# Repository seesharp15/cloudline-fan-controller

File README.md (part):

# Cloudline AI-CLS6 fan controller

A stand-alone speed controller for the **AC Infinity Cloudline AI-CLS6**
(Cloudline S6) EC inline fan. It uses an **Arduino Nano** and an **AITRIP
1.3″ OLED module with a built-in EC11 rotary encoder**, plugs into the fan's
4-pin Molex control lead in place of the stock controller, and runs entirely
from the fan's own 10 V supply.

| Fan off | Fan running (calibrated) |
|---|---|
|  |  |

## What it does

- **Turn the knob** to set the speed from 0 to 100 %: 1 % per click, or 5 %
  per click when you spin it quickly.
- **Press the knob** to switch the fan on or off.
- **The fan is always off at power-up.** A resistor guarantees this in
  hardware before the Arduino even starts, and the firmware starts OFF.
- **The speed setting is kept while the controller has power.** Off and on
  again returns to the same speed. After a power cut it starts OFF at 50 %.
  Nothing is stored permanently.
- **The display shows:**
  - ON/OFF status in the title bar, which turns solid while the fan is on;
  - **SET**: the speed you asked for, as a bar and a percentage;
  - **ACT**: the measured speed from the fan's tachometer, as a bar and a
    percentage of the fan's calibrated top speed;
  - the measured **RPM**.
- **Power:** taken from the fan's +10 V through a resettable fuse,
  reverse-polarity diode, surge clamp and filtering. The controller draws
  about 35–60 mA.
- **Safety nets:** a watchdog stops the fan and restarts the controller if
  the program ever hangs; a "NO TACH / STALLED" warning appears if the fan is
  told to run but no speed pulses arrive.

> ⚠️ **Read before you build.** AC Infinity does not publish the electrical
> details of the control port. The pin functions and signal levels in this
> project come from other builders' reports, and **whether the 4-pin port
> carries a tachometer signal at all is unconfirmed**. The
> [pre-connection verification](#pre-connection-verification) below takes
> about 20 minutes with a multimeter and tells you whether your fan matches.
> Without a tach signal everything works except the ACT bar and RPM.
> [VERIFICATION.md](VERIFICATION.md) lists exactly what has and has not been
> verified.

## Contents

1. [Documents in this repository](#documents-in-this-repository)
2. [Bill of materials](#bill-of-materials)
3. [Tools](#tools)
4. [Software setup](#software-setup)
5. [Pre-connection verification](#pre-connection-verification)
6. [Step-by-step build](#step-by-step-build) (steps 1–6, then
   [7. first power-up](#step-7-first-power-up-on-the-fan-supply) and
   [8. enclosure](#step-8-fit-it-in-the-enclosure))
8. [Normal operation](#normal-operation)
9. [Troubleshooting](#troubleshooting)
10. [Development and tests](#development-and-tests)
11. [Sources](#sources)

---

## Documents in this repository

| Document | Contents |
|---|---|
| [PINOUT.md](PINOUT.md) | Every pin of every part, power rails, point-to-point wiring list |
| [hardware/schematic.svg](hardware/schematic.svg) ([PNG](hardware/schematic.png)) | Full schematic, every part labelled with reference and value |
| [hardware/wiring.svg](hardware/wiring.svg) ([PNG](hardware/wiring.png)) | Physical wiring view with suggested wire colours, for people who don't read schematics |
| [hardware/bom.csv](hardware/bom.csv) | Parts list with part numbers and prices |
| [hardware/pcb/](hardware/pcb/README.md) | **Single-sided PCB** (1 copper layer) as an alternative to perfboard: KiCad project, Gerbers + drill ready to order, assembly drawing, ordering options |
| [hardware/pcb/fusion/](hardware/pcb/fusion/README.md) | **Milling the PCB in Fusion 360** on a Stepcraft M.1000: STEP + DXF (isolation paths, drill layers), Fusion tool library, CAM setup for UCCNC |
| [hardware/pcb/eagle/](hardware/pcb/eagle/README.md) | **Editable design for Fusion Electronics**: schematic + board in EAGLE format |
| [FAQ.md](FAQ.md) | The questions builders ask: USB + fan power, PWM frequency, other fans, warranty, other boards… |
| [BENCH_TEST.md](BENCH_TEST.md) | Manual test of every requirement, first with a dummy load, then with the fan |
| [VERIFICATION.md](VERIFICATION.md) | Requirements traceability, electrical calculations, pin cross-check, what is verified versus assumed, known limitations, review findings |
| [CHANGELOG.md](CHANGELOG.md) | Changes |
| [firmware/](firmware/) | Arduino sketch. Every setting is in [`config.h`](firmware/cloudline_controller/config.h) |
| [test/](test/) | Host unit tests and simulations ([how to run](test/README.md)) |
| [sim/](sim/) | Wokwi simulator files ([what can and cannot be simulated](sim/README.md)) |

---

## Bill of materials

Prices are approximate (USD, 2026) for single quantities. The full list with
manufacturer part numbers is in [hardware/bom.csv](hardware/bom.csv). Any
part with the same value and rating works; the part numbers are examples.

| Ref | Qty | Part | Value / rating | Example part number | ≈ Cost |
|---|---|---|---|---|---|
| U1 | 1 | Arduino Nano | ATmega328P, 5 V, 16 MHz (CH340 clone is fine) | Arduino A000005, or ELEGOO Nano V3.0 | $8 (clone) |
| U3 | 1 | 1.3″ OLED + EC11 module | SH1106, 128×64, I²C 0x3C, 3.3 V | AITRIP 1.3″ OLED with EC11 (Amazon ASIN B0F87DZ51P) | $10 |
| U2 | 1 | 3.3 V LDO regulator | 250 mA, V<sub>in</sub> ≤ 6 V, TO-92 | Microchip MCP1700-3302E/TO | $0.45 |
| Q1 | 1 | N-channel MOSFET | 60 V, 200 mA, logic-level, TO-92 | onsemi 2N7000TA | $0.30 |
| D1 | 1 | Schottky diode | 1 A, 20 V | 1N5817 | $0.20 |
| D2 | 1 | TVS diode, unidirectional | V<sub>RWM</sub> 11.1 V, 600 W | Littelfuse P6KE13A (P6KE15A if your fan measures > 10.8 V) | $0.45 |
| D3, D4 | 2 | Small Schottky diode | 30 V, 200 mA | BAT85 | $0.30 |
| F1 | 1 | Resettable PTC fuse | 0.2 A hold, 0.4 A trip | Bourns MF-R020 | $0.35 |
| U4 | 1 | I²C level shifter module (BSS138) | 5 V ↔ 3.3 V, bidirectional, 2 channels used | SparkFun BOB-12009 | $4 |
| C1 | 1 | Electrolytic capacitor | 220 µF, 25 V | Panasonic EEU-FR1E221 | $0.40 |
| C2 | 1 | Ceramic capacitor | 100 nF, 50 V, 5 mm lead pitch | TDK FG28X7R1H104KNT06 | $0.25 |
| C3, C4 | 2 | Ceramic capacitor | 1 µF, 25 V, 5 mm lead pitch | TDK FG28X7R1E105KRT06 | $0.60 |
| C5 | 1 | Ceramic capacitor | 10 nF, 50 V, 5 mm lead pitch | TDK FG28X7R1H103KNT06 | $0.25 |
| R1, R2 | 2 | Resistor ¼ W 5 % | 2.2 kΩ | Yageo CFR-25JB-52-2K2 | $0.20 |
| R3 | 1 | Resistor ¼ W 5 % | 220 Ω | Yageo CFR-25JB-52-220R | $0.10 |
| R4, R6 | 2 | Resistor ¼ W 5 % | 10 kΩ | Yageo CFR-25JB-52-10K | $0.20 |
| R5 | (1) | Resistor ¼ W 5 %, **only if check M3 says so** | 4.7 kΩ | Yageo CFR-25JB-52-4K7 | $0.10 |
| R7 | 1 | Resistor ¼ W 5 % | 1 kΩ | Yageo CFR-25JB-52-1K0 | $0.10 |
| J1 | 1 | 4-pin PC "Molex" extension cable | male-to-female, 18–20 AWG | StarTech.com LP4POWEXT12 | $4 |
| — | 1 | Perfboard | 5 × 7 cm, 2.54 mm pitch | any | $1 |
| — | 2 | Female header strip (Nano socket) | 1 × 15, 2.54 mm | Sullins PPTC151LFBN-RC | $2 |
| — | 10 | Female-female jumper wires | 20 cm Dupont, for the OLED module | any | $3 |
| — | — | Hook-up wire | 22 AWG stranded (power), 24–26 AWG stranded (signals), several colours | any silicone wire kit | $8 |
| — | — | Heat-shrink tubing | 2–6 mm assortment, 2:1 | any | $6 |
| — | 1 | Enclosure | ABS box, **inside** at least 75 × 60 × 35 mm (perfboard) or 115 × 90 × 35 mm (PCB, so its corners clear the box's screw posts) | a Hammond 1591-series size chosen from its drawing, or 3D-printed | $8 |
| — | 1 | Cable gland | PG7 | any | $0.50 |
| — | 4 | Nylon standoffs and screws | M2.5 or M3 | any | $1 |
| | | | | **Total** | **≈ $60** |

## Tools

| Tool | Notes |
|---|---|
| Temperature-controlled soldering iron | 330–360 °C, small chisel tip |
| Solder | 0.6–0.8 mm rosin-core |
| **Digital multimeter** | Must measure DC volts, resistance, continuity and **diode test**. A frequency (Hz) range is useful for the tach check but not essential. |
| Wire strippers, flush cutters, tweezers | |
| Heat gun or lighter | For heat-shrink |
| **USB cable for the Nano** | Usually **Mini-USB** (some clones use Micro-USB or USB-C). It must be a **data** cable, not charge-only. |
| Computer | Windows, macOS or Linux, with Arduino IDE 2.x |
| 9 V battery with snap lead (or a 9–10 V bench supply with current limit) | For testing the power section before anything touches the fan. Optional but recommended. |
| 220 Ω 1 W resistor, 4.7 kΩ and 10 kΩ ¼ W resistors, 100 Ω ¼ W resistor | For the pre-connection checks (spares from the parts list work) |
| Small drill / step bit, file | For the enclosure window and knob hole |

---

## Software setup

1. **Install the Arduino IDE 2.x** from <https://www.arduino.cc/en/software>
   (2.3.x or newer).
2. **Board support.** Open *Tools → Board → Boards Manager*, search for
   **Arduino AVR Boards**, and install version **1.8.6**. (It is usually
   already installed; just check the version.)
3. **Library.** Open *Tools → Manage Libraries*, search for **U8g2** (by
   oliver), choose version **2.35.30** in the version drop-down, and click
   *Install*. No other library is needed. The pinned versions are listed in
   [firmware/libraries.txt](firmware/libraries.txt).
4. **Open the sketch.** *File → Open* →
   `firmware/cloudline_controller/cloudline_controller.ino`. Five tabs open:
   `cloudline_controller.ino`, `app.cpp`, `config.h`, `display_ui.h`,
   `fan_logic.h`. The folder must stay named `cloudline_controller`.
5. **Select the board.** *Tools → Board → Arduino AVR Boards → Arduino
   Nano*.
6. **USB driver (clone Nanos).** Most clones use a **CH340** USB chip. Plug
   the Nano in and look at *Tools → Port*:
   - A new port appears (`COM3`… on Windows, `/dev/cu.usbserial-…` or
     `/dev/cu.wchusbserial…` on macOS, `/dev/ttyUSB0` on Linux): fine, select it.
   - No new port: install the CH340 driver (**CH341SER**) from the chip maker,
     WCH: <https://www.wch-ic.com/downloads/CH341SER_EXE.html> (Windows) or
     <https://www.wch-ic.com/downloads/CH341SER_MAC_ZIP.html> (macOS), then
     replug. Linux needs no driver. If still nothing, try another USB cable:
     many are charge-only.
7. **Processor setting.** *Tools → Processor* has two choices:
   - **"ATmega328P"**: genuine Nanos and newer clones (Optiboot bootloader,
     uploads at 115200 baud).
   - **"ATmega328P (Old Bootloader)"**: most older and cheap clones
     (uploads at 57600 baud).

   **How to tell:** start with *ATmega328P* and click *Upload* (with any
   sketch, e.g. *File → Examples → 01.Basics → Blink*). If it ends with an
   error like `avrdude: stk500_recv(): programmer is not responding` or
   `not in sync: resp=0x00` after about 10 tries, switch to *Old Bootloader*
   and upload again. Whichever one works is the one you have. The watchdog in
   this firmware is designed to work with both (see
   [FAQ](FAQ.md#what-does-the-watchdog-do-and-is-it-safe-with-the-old-bootloader)).
8. **Compile once** (*Sketch → Verify*). Expected result, give or take a
   few bytes depending on IDE and library versions:

   ```
   Sketch uses 26236 bytes (85%) of program storage space. Maximum is 30720 bytes.
   Global variables use 1287 bytes (62%) of dynamic memory, leaving 761 bytes for local variables. Maximum is 2048 bytes.
   ```

   ("Old Bootloader" shows the same numbers.) Don't upload yet: that is
   build step 5.

Command-line alternative:

```sh
arduino-cli core install arduino:avr@1.8.6
arduino-cli lib install "U8g2@2.35.30"
arduino-cli compile -b arduino:avr:nano firmware/cloudline_controller
arduino-cli upload  -b arduino:avr:nano -p <port> firmware/cloudline_controller
# old bootloader: -b arduino:avr:nano:cpu=atmega328old
```

---

## Pre-connection verification

Do this **before you build anything**, on the fan itself. It confirms the
pin functions, the supply, and the speed signal. You need the multimeter, the
fan plugged into mains, and the resistors listed under Tools. Nothing here
can damage the fan: every test either just measures or goes through a
resistor.

**Setup.** Unplug the stock controller from the fan's control lead. Look
into the lead's 4-pin Molex plug with the two chamfered corners at the top
and number the contacts **1 to 4 from left to right** (picture in
[PINOUT.md §2](PINOUT.md#2-j1-fan-connector-4-pin-molex-pc-peripheral-type-508-mm-pitch)).
The fan may run at full speed while nothing is plugged in. That is expected
and is one of the things being checked. Probe the contacts from the front
with thin probe tips, or plug in the J1 extension cable and probe its loose
end (then follow the wires back to be sure which is which).

Record every reading in a table like the one below; you'll need them later.

| Check | How | Expected | If not → STOP and… |
|---|---|---|---|
| **M1 Supply and ground** | DC volts, black probe on pin 3, red on pin 4 | **+9.5 to +10.5 V** | **Negative reading:** you are numbering from the wrong side; mirror the numbers and repeat. **No pin pair gives 9–11 V:** your fan's port is different (for example a newer USB-C "UIS" port, see [FAQ](FAQ.md#will-this-work-with-other-ac-infinity-fans-or-other-4-pin-fans)). Don't connect. **10.8–12 V:** fit a P6KE15A for D2 instead of P6KE13A. **Over 12 V:** don't connect; the design needs changes. |
| **M2 Supply under load** | Hold a **220 Ω 1 W** resistor across pins 4 and 3 for 5 s and measure pins 4–3 again | Within **0.5 V** of M1 (45 mA load, more than the controller draws) | Drop of more than 1 V: the port can't power the controller. Power the Nano from a separate 9–12 V adapter (FAQ) and leave J1 pin 4 unconnected. |
| **M3 Speed line pull-up** | DC volts, pin 3 (black) to pin 2 (red), nothing else connected | **About the same as M1** (an internal pull-up to the fan's supply) | **Below 1 V or drifting:** the line floats. Fit R5 (4.7 kΩ). **Above M1 + 0.5 V:** don't connect. |
| **M3b Pull-up strength** | Connect a **10 kΩ** resistor from pin 2 to pin 3 and measure pins 2–3 | **Between 1 V and 0.9 × M1** (the internal pull-up is between about 1.1 kΩ and 100 kΩ). Note the value: pull-up R ≈ 10 kΩ × (M3 ÷ reading − 1). While connected, watch the fan for M4b. | **Below 0.1 V:** the pull-up is very weak (> 1 MΩ); fit R5. **Above 0.9 × M1:** pin 2 is a stiff source, not a pulled-up control line. Don't do M4; recheck the numbering. |
| **M4b PWM or analogue input?** | Take the pull-up value you worked out in M3b and connect a resistor of about that value (nearest standard value) from pin 2 to pin 3. The line now sits near **half of M1** (measure it). Wait 15 s and listen. | Either result is fine; note which. **Fan settles at a clearly in-between speed:** the input reacts to the average voltage (analogue-style); the 4 kHz PWM's average does the same job. **Fan runs at full speed or stops:** it is a switching (logic) input, which is what PWM expects. | If later (bench B4) the speed hunts or surges at mid settings, the input is analogue without filtering. Add an RC filter: a series resistor between Q1's drain and J1 pin 2 of **at most 1/20 of the M3b pull-up** (e.g. 470 Ω for a 10 kΩ pull-up), and a capacitor from J1 pin 2 to GND so that the series R × C ≥ 2.5 ms (e.g. 10 µF with 470 Ω). A larger series resistor would stop 0 % / OFF from pulling the line low enough to stop the fan. Re-run M4 and bench B4, B7. |
| **M4 Polarity and stop** | Connect pin 2 to pin 3 through a **100 Ω** resistor. Wait 15 s. Remove it. Wait 15 s. | Linked: the fan **slows down and stops** (it may coast for several seconds). Released: it **speeds up to full**. | **Opposite** (linked = full, released = stop): set `FAN_PWM_INVERTED 0` in `config.h` **and** connect R4 (at the D9 end of R3) to GND instead of +5V. **Linked = slow but never stops:** this fan does not stop at 0 %; OFF will mean "minimum speed" ([FAQ](FAQ.md#does-0-or-off-actually-stop-the-fan)). **No change at all:** pin 2 isn't the speed line; recheck the numbering. |
| **M5 Tach pin** | Fan at full speed (pin 2 released). DC volts pin 3 (black) to pin 1 (red). If your meter has Hz, measure that too. Then connect a **10 kΩ** resistor from pin 1 to pin 4 and repeat. Then stop the fan (100 Ω link on pin 2) and repeat. | A tach shows up as a **frequency of roughly 10–200 Hz while running** (or a steady DC reading between 2 and 8 V that changes when the fan stops), at least with the 10 kΩ pull-up connected. Write down the frequency at full speed. | **Steady 0 V, no frequency in any case:** no tach on this port. The controller still works; ACT shows `--%`. **Steady voltage equal to M1 that doesn't change:** not a tach (another supply pin); it is still safe to connect (R7 limits the current) but there will be no RPM. **Above 12 V:** don't connect pin 1; leave R7 unconnected at J1. |
| **M5b Tach type and pulses per revolution** (optional) | From M5: a frequency **without** the 10 kΩ pull-up means a **push-pull** output (note its high voltage: DC reading ≈ half of it); a frequency only **with** the pull-up means **open collector**. For pulses per revolution you need the true RPM: an optical (laser) tachometer on a piece of reflective tape on the impeller, or a phone slow-motion video of a marked blade at a low setting (count turns per second). PPR = frequency × 60 ÷ RPM. | Usually 1, 2 or 4. Put it in `TACH_PULSES_PER_REV`. | If you can't measure it, leave 2: only the RPM number is affected, not the ACT %. |
| **M6 No short to mains** | Unplug the fan from mains. Ohms, each pin 1–4 to each mains plug blade | **Open circuit (OL)** on every combination | Any reading: the fan is faulty or the port is not isolated. Do not use it. |

**M7 OLED module** (no power needed). With the module unpowered: resistance
VCC to GND **above 1 kΩ**; SDA to VCC and SCL to VCC: either **OL** (no
pull-ups on the module) or **2–10 kΩ** (pull-ups fitted), both fine; TRA,
TRB to GND: **toggles between OL and about 0 Ω** as you turn the knob slowly
(at rest either can be open or closed, depending on the encoder type); PSH to
GND: **OL**, and **0 Ω while pressed**. They are plain switches to GND. If a
pin reads a fixed resistance to VCC instead, the module has its own pull-ups
on the encoder, which is also fine. If SDA/SCL read **4.7 kΩ or less** to
VCC (strong pull-ups already on the module), leave **R1/R2 out** in step 4:
with them as well, the display-side pull-ups would sink more than the 3 mA
I²C allows. The display driver (SH1106 vs SSD1306) and the I²C
address can't be measured with a meter: build step 5 checks them (the
serial console reports which address answers).

When all checks pass, plug the stock controller back in if you still want to
use the fan, and start the build.

---

## Step-by-step build

These steps describe a perfboard build. With the [PCB](hardware/pcb/README.md)
the order and the checks are the same; its README lists which parts go in
at each step.

Build in this order. Each step ends with a check: **don't continue until the
check passes.** The schematic shows every connection; the
[wiring view](hardware/wiring.png) shows where wires go physically; the
[point-to-point list](PINOUT.md#6-point-to-point-wiring-list) is a checklist.

Soldering basics: heat the pad and the lead together for 2–3 s, feed solder
into the joint (not onto the iron), and stop when it flows into a small
shiny cone. Trim leads after soldering. Diodes: the **band is the cathode**.
The electrolytic capacitor: the **stripe marks the negative** lead. TO-92
parts (Q1, U2): read the flat face, legs down, left to right (PINOUT.md §5).

### Step 1. Verify the fan connector

Do the [pre-connection verification](#pre-connection-verification) M1–M6 and
write down the results. Then prepare **J1**: cut the Molex extension cable in
half, keep the end that plugs into the fan's lead, strip 5 mm from each wire,
and **label each wire with its pin number and function** (tape flags). Put
heat-shrink on the cable end.

✅ **Check before continuing:** with J1 plugged into the fan (fan powered),
J1's labelled "+10V" wire reads the M1 voltage against its "GND" wire. Then
unplug J1 from the fan.

### Step 2. Build the power conditioning

On the perfboard, plan three areas (power on the left, Nano socket in the
middle, fan interface near the J1 entry). Solder:

1. the two 15-pin female headers for the Nano socket, 15.24 mm (6 holes) apart;
2. **F1** (PTC), **D1** (1N5817, band towards the Nano VIN side),
   **D2** (P6KE13A, band to +10V_P, other end to GND),
   **C1** (220 µF, stripe to GND), **C2** (100 nF, close to the socket's VIN
   and GND pins);
3. wires: J1 "+10V" to F1, J1 "GND" to the board's GND line, +10V_P to the
   socket's **VIN** pin (30), GND to the socket's **GND** pins (29 and 4).

Do **not** connect J1's PWM and TACH wires yet. Insulate their ends with
heat-shrink.

Before soldering D1 and D2, check them on the meter's diode range: D1
(1N5817) reads **0.15–0.35 V** with red on the plain end and black on the
band, **OL** the other way round; D2 (P6KE13A) reads **0.5–0.8 V** with red
on the plain end, **OL** reversed.

✅ **Check before continuing** (nothing powered):
- Resistance with **red on +10V_P** and black on GND: **not below 1 kΩ** (it
  climbs as C1 charges from the meter, which is normal). With the probes
  reversed you'd see D2 conducting, which is also normal.
- Continuity J1 "GND" to socket pin 29 and pin 4: **beep (< 1 Ω)**.
- Continuity J1 "+10V" to socket pin 30: **no beep** (D1 is in the way).

### Step 3. Test the power section with no Nano

Leave the Nano out of its socket. Connect a 9 V battery (or a bench supply
set to 10.0 V, current limit 100 mA) to J1's +10V and GND wires.

✅ **Check before continuing:**
- Socket VIN (pin 30) to GND: **battery voltage minus 0.05–0.3 V** (D1's
  drop at almost no current; about 9.2 V on a fresh 9 V battery, about
  9.8 V on a 10 V supply).
- Supply current, if your supply shows it: **under 1 mA**.
- **Reverse-polarity test:** swap the battery leads. Socket VIN now reads
  **0 V (±0.1 V)**. D1 is blocking. Swap back.
- D2 and C1 are **not warm** after a minute.

If you'd rather use the fan as the source: plug J1 into the fan with only
the +10V and GND wires attached (PWM and TACH still insulated). Expect VIN =
**M1 minus 0.05–0.3 V**. The fan runs at full speed during this test because
nothing holds its speed line low. Unplug J1 afterwards.

### Step 4. Wire the 3.3 V regulator, OLED and encoder

1. Solder **U2** (MCP1700, flat face towards you: GND, VIN, VOUT),
   **C3** (VIN to GND) and **C4** (VOUT to GND). Wire U2 VIN to the socket's
   **+5V** pin (27).
2. Solder header pins to **U4** (the level-shifter module) and mount it on
   the perfboard. Wire **HV** to +5V (socket pin 27), **LV** to U2 VOUT
   (+3V3), **GND** to GND, **HV1** to socket **A4** (pin 23), **HV2** to
   socket **A5** (pin 24). U4 lets the 5 V Nano and the 3.3 V display talk
   without either seeing the other's voltage.
3. Solder **R1** (U2 VOUT to U4 **LV1**) and **R2** (U2 VOUT to U4 **LV2**),
   unless check M7 found 4.7 kΩ or less pull-ups on the module.
4. Run the module wires, **matching the labels printed on your module**
   (the pin order varies between batches):

   | Module | To | Suggested colour |
   |---|---|---|
   | VCC | U2 VOUT (+3V3) | pink |
   | GND | GND | black |
   | SDA | U4 LV1 (and R1); U4 HV1 goes to socket A4 (pin 23) | blue |
   | SCL | U4 LV2 (and R2); U4 HV2 goes to socket A5 (pin 24) | white |
   | TRA | socket D3 (pin 6) | purple |
   | TRB | socket D4 (pin 7) | grey |
   | PSH | socket D5 (pin 8) | cyan |
   | CON | socket D6 (pin 9) (optional) | light blue |
   | BAK | socket D7 (pin 10) (optional) | violet |

✅ **Check before continuing** (nothing powered, Nano out):
- Continuity from each module pin to its socket pin in the table: **beep**
  (for SDA/SCL: module to U4 LV1/LV2, and U4 HV1/HV2 to A4/A5).
- No continuity between neighbouring socket pins D3–D7, or A4–A5.
- No continuity from socket A4 to module SDA (U4 is in between: you'll read
  several kΩ, not a beep).
- Resistance socket +5V (27) to GND: **above 1 kΩ**.
- Resistance module VCC to GND: **above 1 kΩ**.
- Resistance module SDA to module VCC: **2.2 kΩ or less** (R1, perhaps in
  parallel with a pull-up on the module).

### Step 5. Flash and test with USB power only

J1 must **not** be connected to anything.

**Orientation check before plugging in the Nano.** In step 2 you wired one
socket hole to +10V_P (via D1) and the hole next to it to GND; in step 4 you
wired a hole three places further along to +5V. Hold the Nano over the
socket: the pins printed **VIN**, **GND** and **5V** must sit over exactly
those holes. Turned round the other way, VIN would land on D12 and the
Nano could be damaged as soon as the fan powers it. Then plug the Nano in,
connect USB, select the port and processor (Software setup step 7), and
click **Upload**.

✅ **Check before continuing:**
- The IDE ends with `Done uploading` (or avrdude reports
  `... bytes of flash verified`).
- Within 1 s the display shows **`FAN OFF`** in an outlined title bar,
  **`0 RPM`** at the right, **SET** bar at **50%**, **ACT** at **`--%`**, and
  the footer **`Press knob to start`** (like the left picture at the top).
- Multimeter: socket +5V to GND **4.5–5.1 V** (USB minus the Nano's diode);
  module VCC to GND **3.25–3.35 V**.
- Turn the knob slowly one click clockwise: SET becomes **51%**. One click
  back: **50%**. If it goes the wrong way, set `ENC_REVERSE 1` in `config.h`
  and upload again. If every *other* click is ignored, set
  `ENC_EDGES_PER_DETENT 2`.
- Press the knob once: title becomes a solid **`FAN ON`** and the Nano's
  **L** LED (D13) lights. After 8 s the footer shows
  **`! NO TACH / STALLED`**: correct, there is no fan yet. Press again: back
  to `FAN OFF`, LED off.
- *Tools → Serial Monitor*, **115200** baud, line ending **Newline**. On
  reset it prints `Cloudline controller ready. Fan OFF. Send ? for help.`
  and **`OLED answers at 0x3C`**. Type `s` and Enter: a status line
  starting `on=0 set=50%` appears.
- Display driver: the picture is sharp and centred with no column of random
  dots at either edge. If there is one, your module has an SSD1306: set
  `OLED_SSD1306 1` and upload again.

### Step 6. Wire the fan interface

Unplug USB. Solder:

1. **Speed output:** **Q1** (2N7000, flat face towards you: S, G, D);
   **R3** 220 Ω from socket **D9** (pin 12) to Q1 gate; **R4** 10 kΩ from
   the **D9 end of R3** to **+5V**; Q1 source to GND; J1 **PWM** wire to Q1 drain.
   Fit **R5** (Q1 drain to J1's +10V wire, before F1) only if check M3
   told you to.
2. **Tach input:** **R7** 1 kΩ from J1 **TACH** wire to the tach node;
   from the tach node: **R6** 10 kΩ to +5V, **D3** BAT85 (band to +5V),
   **D4** BAT85 (band to the tach node, other end GND), **C5** 10 nF to GND,
   and a wire to socket **D2** (pin 5). If M5 found more than 12 V on pin 1,
   leave the TACH wire unconnected.

✅ **Check before continuing** (J1 still unplugged from the fan; USB
connected, so the Nano runs):
- Q1 gate (the R3/Q1 junction) to GND with the display at **`FAN OFF`**:
  **4.5–5.1 V**. Gate high means Q1 is on, which means the fan line is held
  low.
- Press the knob (`FAN ON`), turn SET to **100%**: gate **below 0.1 V**.
- SET **50%**: the meter (DC volts) shows about **half the 5 V reading**
  (2.2–2.6 V). It is averaging the 4 kHz PWM.
- Switch OFF again. Resistance with the **red** probe on J1 **PWM** and the
  **black** probe on J1 **GND**: **below 20 Ω** (Q1 is on). Switch ON at
  100 %: **above 1 MΩ** or OL (Q1 is off). With the probes the other way
  round you'd measure Q1's internal diode instead. (Skip this if R5 is
  fitted; Step 7 and BENCH_TEST cover it with voltages.)
- Tach node (socket D2) to GND: **4.5–5.1 V** (R6 pull-up).
- Touch J1 **TACH** to J1 **GND** for a moment: the tach node drops to
  **about 0.45 V** while touching. Press **CON** (or hold the knob while
  pressing reset) to open the diagnostics page: the **`n=`** counter at top
  right goes up each time you touch.

---

## Step 7. First power-up on the fan supply

1. Unplug USB from the Nano. Unplug the fan from mains.
2. Plug J1 into the fan's control lead.
3. Plug the fan into mains.

**What you should see within about 1 second:**

| | Expected |
|---|---|
| Fan | **Not running.** If it was spinning, it coasts to a stop. |
| Display | **`FAN OFF`**, `0 RPM`, SET **50%**, ACT **`--%`**, footer **`Press knob to start`** |
| Nano LED L (D13) | off |
| +10V_P (socket VIN) to GND | **M1 minus 0.2–0.7 V** |
| +5V (socket 27) to GND | **4.9–5.1 V** |
| Module VCC to GND | **3.25–3.35 V** |

Then:

4. **Press the knob.** `FAN ON` (solid title bar). The fan starts at 50 %.
   Within 1–3 s the RPM figure shows a number; ACT stays at `--%` because the
   fan's top speed isn't known yet, and the footer reads
   **`Hold knob 3s: CAL`**. (No RPM after 8 s and the footer says
   `! NO TACH / STALLED`? See [Troubleshooting](#troubleshooting).)
5. **Turn the knob** to 100 % and back to 20 %: the fan speeds up and slows
   down within a few seconds (EC fans ramp gently).
6. **Calibrate** (needs a tach): set any speed, then **hold the knob for 3
   seconds** until the footer countdown finishes. The fan runs at 100 % for
   18 s (12 s spin-up, 6 s measuring) and shows **`CAL DONE`** with the
   top-speed RPM. Then ACT shows real percentages.
7. **Press the knob.** `FAN OFF`, the fan stops.
8. Unplug the fan from mains, wait 10 s, plug it back in. The controller
   comes up **OFF at 50 %** again.

✅ **Check before continuing:** every row of the table above matched, and
steps 4–8 behaved as described.

Optional, recommended: work through [BENCH_TEST.md](BENCH_TEST.md), which
tests every requirement one by one.

## Step 8. Fit it in the enclosure

Unplug the fan from mains first. Cut a window for the OLED and a hole for
the encoder shaft (usually 7 mm), fit the cable gland for J1, mount the
perfboard and the module on standoffs, and make sure the Nano's USB socket
can still be reached. Tie a knot or use the gland so a pull on the fan cable
can't reach the solder joints. Check that no bare lead touches another or
the Nano's underside.

✅ **Check before continuing:** plug the fan back into mains. The display
shows `FAN OFF` and the fan doesn't run; press the knob and it runs.

---

## Normal operation

| Control | What it does |
|---|---|
| Turn the knob | Change the speed setting. 1 % per click; 5 % per click if you turn quickly. Works while OFF too (the fan stays off). |
| Press the knob (short) | Fan ON / OFF. The toggle happens when you **release** the knob, so that a long hold can start a calibration instead. |
| Hold the knob 3 s (fan ON) | Calibrate the top speed. Press the knob or BAK to cancel. |
| CON key | Diagnostics page (raw tach Hz, pulse count, line duty, PWM register values). CON or BAK returns. |
| BAK key | Back to the main screen; cancels a calibration. |
| Knob held while powering up | Start on the diagnostics page (that press doesn't switch the fan on). |

**The screen** (refreshes 10 times a second, and immediately after you
turn or press the knob):

| Screen | Meaning |
|---|---|
|  | Fan OFF. SET shows the speed it will run at when switched on. |
|  | Fan ON, RPM measured, top speed not calibrated yet: ACT shows `--%`. |
|  | Fan ON and calibrated. The thin vertical line in the ACT bar marks the SET value. |
|  | The fan was told to run but no tach pulses arrived for 8 s. |
|   | Calibration countdown, and the calibration run. |
|   | Calibration result. |
|  | Diagnostics page. |

**Keeping the calibration.** By design nothing is stored permanently, so a
calibration lasts until power-off. To make it permanent, connect USB once,
open the Serial Monitor (115200 baud) and calibrate: it prints a line such as
`#define TACH_MAX_RPM 1836`. Put that number into `config.h` and upload again.

**Serial console** (115200 baud, Newline): `?` help · `s` status ·
`on` / `off` · `set 40` · `c` calibrate (fan must be on) · `x` cancel ·
`m 1836` set top speed for this session. You can leave USB connected while
the fan is plugged in ([FAQ](FAQ.md#can-i-power-the-nano-from-usb-and-the-fan-at-the-same-time)).

---

## Troubleshooting

| Symptom | Likely cause | Fix |
|---|---|---|
| **Blank display**, LED L works (the controller keeps working without a display and looks for it again every 5 s) | No 3.3 V at the module; SDA/SCL swapped or not connected; U4 not powered; module at address 0x3D; wrong module pin order | Open the Serial Monitor: it says whether a display answers and at which address (`OLED answers at 0x3C`, or `! but a device answers at 0x3D`). Measure module VCC (3.25–3.35 V) and U4 HV (5 V) / LV (3.3 V). Check SDA/SCL by label, not position. |
| **Blank display**, nothing works | No power: F1 tripped, D1 reversed, J1 wires swapped | Measure VIN (Step 3 values). Unplug, let F1 cool for a minute, look for a short. |
| **Garbled display** (random dots, shifted picture, a column of noise at one edge) | Your board has an SSD1306, not an SH1106 | Set `OLED_SSD1306 1` in `config.h` and upload. |
| **Garbled display** that changes when the fan starts | Noise or a poor ground on the I²C wires | Keep the OLED wires short (< 30 cm) and away from the fan cable; check the GND wire to the module. |
| **Encoder skips** clicks (every other click ignored) | Encoder has 2 edges per click (15 pulses / 30 detents type) | `ENC_EDGES_PER_DETENT 2` |
| **Encoder jumps 2 per click** | The opposite: `ENC_EDGES_PER_DETENT` is 2 on a 20/20 encoder | `ENC_EDGES_PER_DETENT 4` |
| **Encoder runs backwards** | A/B swapped (module orientation) | `ENC_REVERSE 1`, or swap the TRA/TRB wires |
| **Encoder erratic** | Loose TRA/TRB/GND wire | Recheck Step 4 continuity |
| **Button doesn't toggle** | PSH not on D5, or no GND to the module | Continuity PSH → D5. Note the toggle happens on **release**; if you hold for 3 s it starts a calibration instead (only while ON). |
| **Button toggles twice** | Should not happen: presses are debounced (25 ms). If it does, the switch is failing. | Raise `BUTTON_DEBOUNCE_MS` to 50. |
| **Fan runs at full speed when it should be off** (display says FAN OFF) | Q1 not pulling the line low: Q1 backwards, R4 missing, PWM wire on the wrong J1 pin, or polarity opposite | Q1 gate should read ~5 V while OFF (Step 6). Check 2N7000 pin order S-G-D. Recheck M4; if the fan runs when the line is low, use `FAN_PWM_INVERTED 0` and R4 to GND. |
| **Fan runs at full speed for a moment at power-up** | R4 missing or wired to the wrong place | R4 must go from the D9 end of R3 to +5V. |
| **Fan won't stop at 0 % / OFF** (runs slowly) | This fan's minimum speed is above zero when the line is low (M4) | Expected for that fan: see [FAQ](FAQ.md#does-0-or-off-actually-stop-the-fan). |
| **Fan won't stop and runs at full** | See "full speed when it should be off" | |
| **Fan doesn't start at low settings** | EC fans need a minimum duty to start | Raise `FAN_DUTY_MIN_PCT` to the lowest duty that turns it (BENCH_TEST B6). |
| **Speed tops out at about half** | Line not reaching the fan's high level: R5 fitted when not needed, or something else loads the line | Remove R5 if M3 read ~10 V. Q1 must be fully off at 100 % (gate < 0.1 V). |
| **RPM reads 0 / "NO TACH"** while the fan clearly turns | No tach on this port (M5), TACH wire on the wrong pin, D4 backwards, or `TACH_FAULT_MS` too short for a slow-starting fan | Diagnostics page: does `n=` count? Recheck M5. D4 band must face the tach node. |
| **RPM erratic** or jumps | Noise on the tach wire, or a tach signal with slow edges | Route the tach wire away from mains; C5 must be fitted. Increase `TACH_WINDOW_MS` to 1000 or `TACH_SMOOTHING` to 8. |
| **RPM is exactly double or half the real speed** | Pulses per revolution differ from 2 | Change `TACH_PULSES_PER_REV` (ACT % is unaffected; it uses the calibration). |
| **ACT always `--%`** while RPM shows | Not calibrated in this power session | Hold the knob 3 s while ON, or set `TACH_MAX_RPM` in `config.h` |
| **CAL FAILED** | No tach, or the speed varied by more than ±10 % at 100 % (gusty ducting, fan still ramping) | Check the tach; close doors/vents; try again. Raise `CAL_SPINUP_MS` for a slow fan. |
| **Nano resets when the fan changes speed** (display flickers back to FAN OFF) | The fan's 10 V dips under load changes; poor connection in J1; C1 missing | Check J1 crimp and solder joints. C1 must be 220 µF or more (470 µF is fine). Measure VIN during a speed change: it must stay above 6.5 V. |
| **Display goes back to FAN OFF on its own**, serial says `restarted by the watchdog` | The program stalled for 2 s (should not happen) | Note what you were doing and open an issue. The fan is safely OFF after a restart. |
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
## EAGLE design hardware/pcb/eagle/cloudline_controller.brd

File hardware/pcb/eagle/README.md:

# Editable design for Fusion Electronics (EAGLE format)

Fusion 360's electronics workspace reads EAGLE 9 files. These two files are
the KiCad board in that format. Opened together, they become a linked
schematic and PCB that you can edit.

| File | What it is |
|---|---|
| [`cloudline_controller.sch`](cloudline_controller.sch) | Schematic: all 24 parts and 20 nets, joined by net labels |
| [`cloudline_controller.brd`](cloudline_controller.brd) | Board: 100 × 75 mm outline, 4 M3 holes, every part at its KiCad position, all 100 track segments on **Bottom (16)**, silkscreen, design rules |
| [`schematic_preview.png`](schematic_preview.png) | What the schematic sheet looks like |
| [`make_eagle.py`](make_eagle.py) | Generates the two files from `../cloudline_controller.kicad_pcb` |
| [`check_eagle.py`](check_eagle.py) | Checks them (see below) |
| [`eagle.dtd`](eagle.dtd) | EAGLE 9.1.3 file-format DTD from Autodesk (CC BY-ND 3.0, unmodified), used by the check |
| [`preview_schematic.py`](preview_schematic.py) | Draws `schematic_preview.png` |

Both files embed the library **cloudline**:

- the packages are made from the KiCad footprints, with the enlarged
  single-sided pads;
- each part has its own symbol and device;

so no other library is needed.

## Opening in Fusion 360

1. In the **Data Panel**, choose *Upload* and select **both**
   `cloudline_controller.sch` and `cloudline_controller.brd` in one go.
   Fusion converts EAGLE files into an electronics design. Uploading the pair
   together keeps the schematic and the board linked, so changes are kept in
   sync between them.
2. Open the design and run **ERC** on the schematic and **DRC** on the board.
   The board carries the rule set `cloudline_single_sided`:
   - 0.6 mm clearance;
   - 0.4 mm minimum track width;
   - 0.8 mm copper to edge;
   - two net classes, *default* (0.5 mm tracks) and *power* (0.8 mm tracks).

## Things to know when editing

- **Single-sided.** Route only on the **Bottom** layer. In EAGLE and Fusion,
  a through-hole pad always has copper on Top and Bottom, so the 3D PCB shows
  a ring on the top side too. On the milled or etched board that ring does not
  exist. Only Bottom copper is cut.
- **Schematic style.** The parts are connected by **net labels** (a short
  stub with the net name on each pin), not by drawn wires. Pins with the same
  label are the same net. The drawn circuit diagram with explanations is
  [`../../schematic.png`](../../schematic.png).
- **Pad shapes.**
  - EAGLE pads are round or square. Pads that were round or square in KiCad
    keep the same shape and size.
  - The 12 slightly oval BOB-12009 pads (1.9 × 2.0 mm) become round
    1.9 mm pads.
  - Restring settings never make a pad smaller than its package size.
- **Which copy is master.** This repository's master copy is the KiCad project.
  The milling files in [`../fusion/`](../fusion/README.md) and the Gerbers in
  [`../fab/`](../fab/) are made from it. If you change the board in Fusion,
  those files no longer match. Machine the edited board from Fusion itself
  (its 3D PCB, or a Gerber/CAM export of the Bottom layer).

## How the files are checked

`python3 hardware/pcb/eagle/check_eagle.py` (KiCad 7 and lxml needed):

1. **Both files are valid** against EAGLE's DTD.
2. **The board is read back with KiCad's own EAGLE importer**, independent
   of the code that wrote it. The check then confirms:
   - all 95 pads are at the same position as on the KiCad board (worst error
     0.0000 mm), with the same size, drill and net;
   - the 100 track segments are identical;
   - KiCad finds 0 unconnected items;
   - `../check_pcb.py`, which checks the copper against PINOUT.md, passes on
     the imported board: 20 nets, 71 pads, 0 problems.
3. **The schematic is checked geometrically:**
   - every net stub starts exactly on its pin's real position, on the
     0.1 inch grid;
   - every label sits on its stub;
   - no two pins share a point;
   - the device pin-to-pad maps give exactly the board's netlist.

A mutation test (rotating one part, re-pinning one net) made the check fail as
expected. What has **not** been tested is opening the files in Fusion 360
itself. Fusion isn't available here.

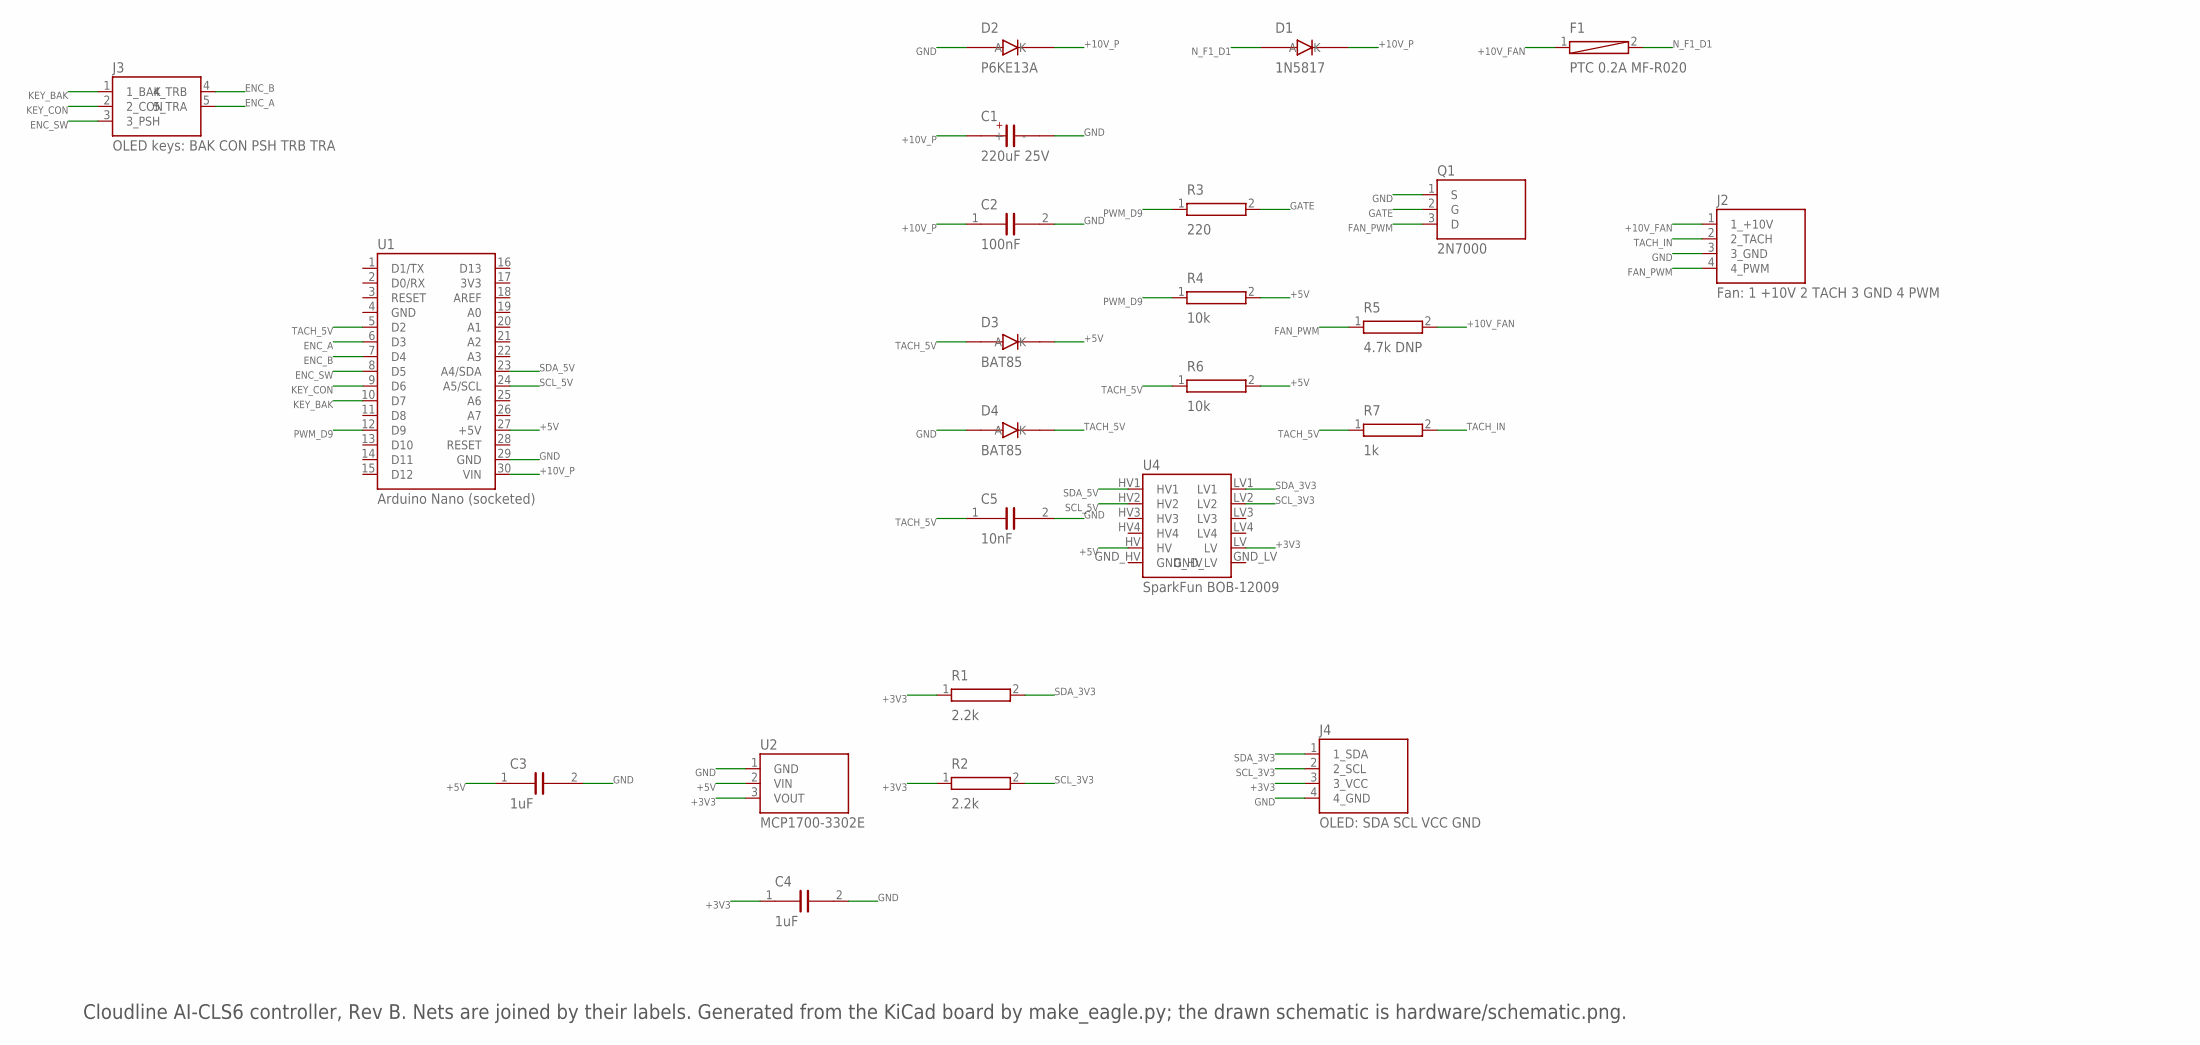
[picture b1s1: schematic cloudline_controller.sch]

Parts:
C1: 220uF 25V; CP_Radial_D8.0mm_P3.50mm
C2: 100nF; C_Disc_D5.0mm_W2.5mm_P5.00mm
C3, C4: 1uF; C_Disc_D5.0mm_W2.5mm_P5.00mm
C5: 10nF; C_Disc_D5.0mm_W2.5mm_P5.00mm
D1: 1N5817; D_DO-41_SOD81_P10.16mm_Horizontal
D2: P6KE13A; D_DO-15_P12.70mm_Horizontal
D3, D4: BAT85; D_DO-34_SOD68_P7.62mm_Horizontal
F1: PTC 0.2A MF-R020; PTC_Radial_P5.10mm
J2: Fan: 1 +10V 2 TACH 3 GND 4 PWM; TerminalBlock_Phoenix_MKDS-1_5-4-5.08_1x04_P5.08mm_Horizont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
J3: OLED keys: BAK CON PSH TRB TRA; PinHeader_1x05_P2.54mm_Vertical
J4: OLED: SDA SCL VCC GND; PinHeader_1x04_P2.54mm_Vertical
Q1: 2N7000; TO-92_Inline_Wide
R1, R2: 2.2k; R_Axial_DIN0207_L6.3mm_D2.5mm_P2.54mm_Vertical
R3: 220; R_Axial_DIN0207_L6.3mm_D2.5mm_P7.62mm_Horizontal
R4: 10k; R_Axial_DIN0207_L6.3mm_D2.5mm_P10.16mm_Horizontal
R5: 4.7k DNP; R_Axial_DIN0207_L6.3mm_D2.5mm_P10.16mm_Horizontal
R6: 10k; R_Axial_DIN0207_L6.3mm_D2.5mm_P7.62mm_Horizontal
R7: 1k; R_Axial_DIN0207_L6.3mm_D2.5mm_P10.16mm_Horizontal
U1: Arduino Nano (socketed); Arduino_Nano
U2: MCP1700-3302E; TO-92_Inline_Wide
U4: SparkFun BOB-12009; SparkFun_BOB-12009

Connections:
+3V3: C4.1, J4.3 (3_VCC), R1.1, R2.1, U2.3 (VOUT), U4.LV
+5V: C3.1, D3.1 (K), R4.2, R6.2, U1.27 (+5V), U2.2 (VIN), U4.HV
+10V_FAN: F1.1, J2.1 (1_+10V), R5.2
+10V_P: C1.1 (+), C2.1, D1.1 (K), D2.1 (K), U1.30 (VIN)
ENC_A: J3.5 (5_TRA), U1.6 (D3)
ENC_B: J3.4 (4_TRB), U1.7 (D4)
ENC_SW: J3.3 (3_PSH), U1.8 (D5)
FAN_PWM: J2.4 (4_PWM), Q1.3 (D), R5.1
GATE: Q1.2 (G), R3.2
GND: C1.2 (-), C2.2, C3.2, C4.2, C5.2, D2.2 (A), D4.2 (A), J2.3 (3_GND), J4.4 (4_GND), Q1.1 (S), U1.29 (GND), U2.1 (GND)
KEY_BAK: J3.1 (1_BAK), U1.10 (D7)
KEY_CON: J3.2 (2_CON), U1.9 (D6)
N_F1_D1: D1.2 (A), F1.2
PWM_D9: R3.1, R4.1, U1.12 (D9)
SCL_3V3: J4.2 (2_SCL), R2.2, U4.LV2
SCL_5V: U1.24 (A5/SCL), U4.HV2
SDA_3V3: J4.1 (1_SDA), R1.2, U4.LV1
SDA_5V: U1.23 (A4/SDA), U4.HV1
TACH_5V: C5.1, D3.2 (A), D4.1 (K), R6.1, R7.1, U1.5 (D2)
TACH_IN: J2.2 (2_TACH), R7.2

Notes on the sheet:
Cloudline AI-CLS6 controller, Rev B. Nets are joined by their labels. Generated from the KiCad board by make_eagle.py; the drawn schematic is hardware/schematic.png.

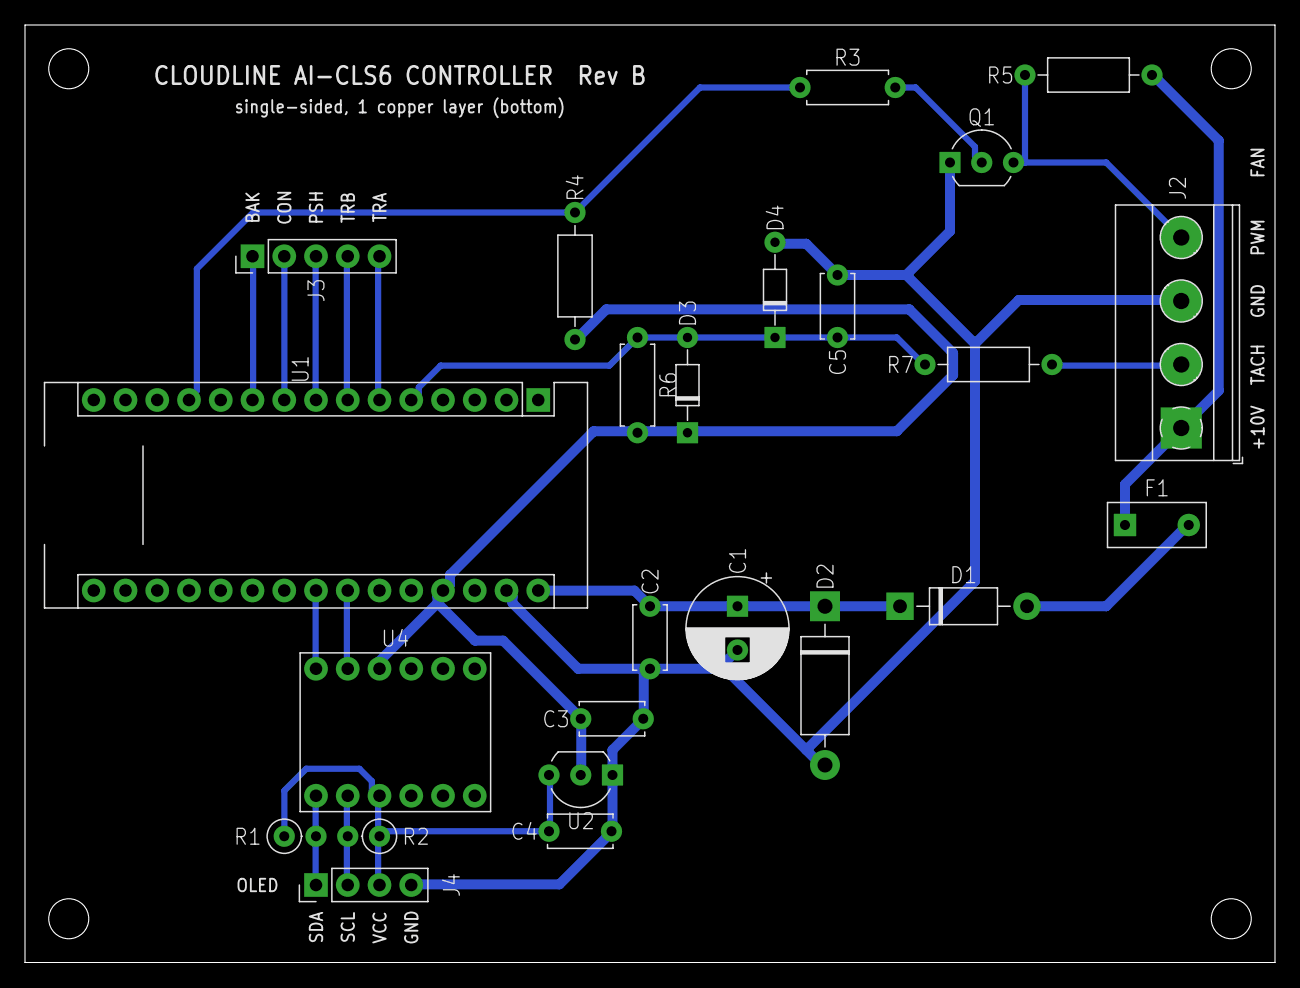
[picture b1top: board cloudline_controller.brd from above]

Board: 2 copper layers, 100.0 x 75.0 mm, 24 parts (0 on the bottom side), 20 nets.

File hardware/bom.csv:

Ref,Qty,Part,Value / rating,Example part number or listing,Package,Approx. unit cost (USD),Notes
U1,1,Arduino Nano (ATmega328P 5 V 16 MHz),Clone with CH340 USB chip is fine,Arduino A000005 (genuine) or ELEGOO Nano V3.0 3-pack (Amazon),Module,8.00,Clone ~$5-8; genuine ~$25. Get one with headers NOT soldered if you will socket it.
U3,1,1.3in OLED + EC11 encoder module,SH1106 128x64 I2C 0x3C; 3.3 V; EC11 20 pulses/20 detents,AITRIP 1.3 inch OLED with EC11 (Amazon ASIN B0F87DZ51P),Module,10.00,Pin labels VCC GND SDA SCL TRA TRB PSH CON BAK; order varies by batch
U2,1,LDO regulator 3.3 V,MCP1700 3.3 V 250 mA; Vin max 6 V,Microchip MCP1700-3302E/TO,TO-92,0.45,Pinout flat face towards you: GND VIN VOUT (check datasheet). PCB: bend the outer leads out to 2.54 mm pitch
Q1,1,N-channel MOSFET,60 V; 200 mA; Vgs(th) 0.8-3 V; Rds(on) <= 5.3 ohm at 4.5 V,onsemi 2N7000TA (or 2N7000BU),TO-92,0.30,Pinout flat face towards you: S G D. PCB: 2.54 mm pitch; bend straight 1.27 mm leads out
D1,1,Schottky diode (reverse-polarity),1 A 20 V,onsemi 1N5817RLG (or Vishay 1N5817-E3/54),DO-41,0.20,Band = cathode = towards +10V_P
D2,1,TVS diode unidirectional,Vrwm 11.1 V; Vbr 12.4-13.7 V; 600 W,Littelfuse P6KE13A,DO-15,0.45,Use P6KE15A if the fan rail measures above 10.8 V
D3 D4,2,Small-signal Schottky diode (tach clamps),30 V 200 mA,Nexperia BAT85 (BAT85.133) or Vishay BAT85-TAP,DO-34,0.15,Band = cathode. D3 cathode to +5V; D4 cathode to tach node
F1,1,PTC resettable fuse,0.20 A hold; 0.40 A trip; 60 V,Bourns MF-R020,Radial 5.1 mm,0.35,PCB footprint: straight leads 5.1 mm apart
C1,1,Aluminium electrolytic capacitor,220 uF 25 V (or 35 V) 105 C,Panasonic EEU-FR1E221 (or Nichicon UVR1E221MED),Radial 8 mm,0.40,Observe polarity: stripe = negative
C2,1,Ceramic capacitor,100 nF 50 V X7R,TDK FG28X7R1H104KNT06,Radial 5.0 mm,0.25,5 mm lead pitch fits the PCB footprint
C3 C4,2,Ceramic capacitor,1 uF 25 V X7R,TDK FG28X7R1E105KRT06,Radial 5.0 mm,0.30,MCP1700 needs >= 1 uF on input and output; 5 mm lead pitch for the PCB
C5,1,Ceramic capacitor,10 nF 50 V X7R,TDK FG28X7R1H103KNT06,Radial 5.0 mm,0.25,PCB needs 5 mm lead pitch (FG28 family; check the datasheet of the exact part)
U4,1,Bidirectional I2C level shifter (BSS138),2 channels used; 5 V HV side / 3.3 V LV side; 10 kohm pull-ups on board,SparkFun BOB-12009,Module,3.95,Between Nano A4/A5 (HV) and OLED SDA/SCL (LV). Solder header pins.
R1 R2,2,Resistor,2.2 kohm 1/4 W 5 %,Yageo CFR-25JB-52-2K2,Axial,0.10,I2C pull-ups to +3V3 (2.2k for 400 kHz rise time)
R3,1,Resistor,220 ohm 1/4 W 5 %,Yageo CFR-25JB-52-220R,Axial,0.10,Q1 gate series
R4,1,Resistor,10 kohm 1/4 W 5 %,Yageo CFR-25JB-52-10K,Axial,0.10,Q1 gate pull-up: keeps fan OFF during reset/boot
R5,1,Resistor (do not populate by default),4.7 kohm 1/4 W 5 %,Yageo CFR-25JB-52-4K7,Axial,0.10,Fit only if the PWM line floats (pre-connection check M3)
R6,1,Resistor,10 kohm 1/4 W 5 %,Yageo CFR-25JB-52-10K,Axial,0.10,Tach pull-up to +5V
R7,1,Resistor,1 kohm 1/4 W 5 %,Yageo CFR-25JB-52-1K0,Axial,0.10,Tach series / clamp current limit
J1,1,4-pin PC peripheral (Molex 8981) extension cable,Male-to-female; 18-20 AWG; 30 cm,StarTech.com LP4POWEXT12 (or any 4-pin Molex extension),Cable,4.00,Cut in half; keep the end that plugs into the fan's control lead (PCB: its wires go into J2)
-,1,Perfboard (protoboard) - perfboard build only,5 x 7 cm double-sided 2.54 mm pitch,ElectroCookie or generic 5x7 cm FR4 protoboard,Board,1.00,Not needed with the PCB
-,2,Female header strip for Nano socket,1 x 15 pin 2.54 mm,Sullins PPTC151LFBN-RC,Through-hole,1.00,Lets you unplug the Nano; optional
-,1,Female-female jumper wires (OLED module),20 cm 2.54 mm Dupont; 10 needed,Generic 40-pin F-F Dupont ribbon (Amazon),Wire,3.00,Or solder 24-26 AWG wire directly
-,1,Hook-up wire,22 AWG stranded (power) and 24-26 AWG stranded (signals); several colours,Generic silicone wire kit (e.g. Striveday 22 AWG 6 colours),Wire,8.00,Colours per hardware/wiring.svg
-,1,Heat-shrink tubing assortment,2-6 mm 2:1 polyolefin,Generic 2:1 assortment kit,Tubing,6.00,For the J1 cable splices and exposed leads
-,1,Enclosure,"ABS box; INSIDE at least 115 x 90 x 35 mm for the PCB (100 x 75 mm board clear of corner screw posts), or 75 x 60 x 35 mm for the perfboard","e.g. a Hammond 1591-series box chosen from its drawing (inside size and boss positions), or 3D-printed",Box,8.00,Mount the board on 4 x M3 standoffs through its own holes; cut a window for the OLED and a 7 mm hole for the encoder shaft
-,1,Cable gland,PG7 for 3-6.5 mm cable,Generic nylon PG7 gland,Hardware,0.50,Strain relief for the fan cable
-,4,Standoffs and screws,M2.5 or M3 x 6-10 mm nylon,Generic nylon standoff kit,Hardware,0.25,Mount the perfboard and OLED module
-,1,Knob for EC11 D-shaft,6 mm,Generic 6 mm D-shaft knob,Hardware,1.00,Optional; some modules include one
PCB,1,Printed circuit board - PCB build only,"100 x 75 mm, 1 copper layer, FR-4 1.6 mm",hardware/pcb/fab/cloudline_controller_RevB_gerbers_drill.zip (order from any board house),Board,2.00,Replaces the perfboard; see hardware/pcb/README.md
J2,1,4-way screw terminal - PCB build only,5.08 mm pitch; 1.5 mm2 wire,Phoenix Contact MKDS 1/4-5.08 (1715747),Through-hole,1.50,Fan cable connection: 1 +10V 2 TACH 3 GND 4 PWM (labelled on the board)
J3,1,Pin header - PCB build only,1 x 5 male 2.54 mm,Generic 2.54 mm break-away male header,Through-hole,0.10,OLED keys/encoder (BAK CON PSH TRB TRA)
J4,1,Pin header - PCB build only,1 x 4 male 2.54 mm,Generic 2.54 mm break-away male header,Through-hole,0.10,OLED power/I2C (SDA SCL VCC GND)

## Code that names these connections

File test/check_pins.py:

#!/usr/bin/env python3
"""Cross-check every pin assignment across the firmware, the schematic, the
wiring view, PINOUT.md and README.md. Exits non-zero on any mismatch.

    python3 test/check_pins.py        (from the repository root)
"""

import os
import re
import sys

ROOT = os.path.dirname(os.path.dirname(os.path.abspath(__file__)))


def read(rel):
    with open(os.path.join(ROOT, rel), encoding="utf-8") as f:
        return f.read()


# Arduino Nano physical pin numbers (header pin 1 = D1/TX).
NANO_PHYS = {"D1": 1, "D0": 2, "GND_A": 4, "D2": 5, "D3": 6, "D4": 7, "D5": 8, "D6": 9,
             "D7": 10, "D8": 11, "D9": 12, "D10": 13, "D11": 14, "D12": 15, "D13": 16,
             "3V3": 17, "A4": 23, "A5": 24, "5V": 27, "GND_B": 29, "VIN": 30}

# signal: (config.h macro or None, Nano pin, module label or None, wiring.py net)
SIGNALS = [
    ("TACH", "PIN_TACH", "D2", None, "TACH_D2"),
    ("ENC_A", "PIN_ENC_A", "D3", "TRA", "TRA"),
    ("ENC_B", "PIN_ENC_B", "D4", "TRB", "TRB"),
    ("ENC_SW", "PIN_ENC_SW", "D5", "PSH", "PSH"),
    ("KEY_CON", "PIN_KEY_CON", "D6", "CON", "CON"),
    ("KEY_BAK", "PIN_KEY_BAK", "D7", "BAK", "BAK"),
    ("FAN_PWM", "PIN_FAN_PWM", "D9", None, "GATE"),
    ("STATUS_LED", "PIN_STATUS_LED", "D13", None, None),
    ("SDA", None, "A4", "SDA", "SDA"),
    ("SCL", None, "A5", "SCL", "SCL"),
    ("VIN", None, "VIN", None, "VIN"),
    ("+5V", None, "5V", None, "+5V"),
]

rows = []
failures = 0


def check(name, source, ok, detail=""):
    global failures
    rows.append((name, source, "ok" if ok else "MISMATCH", detail))
    if not ok:
        failures += 1


cfg = read("firmware/cloudline_controller/config.h")
sch = read("hardware/schematic.py")
wir = read("hardware/wiring.py")
pin = read("PINOUT.md")
rd = read("README.md")

# Schematic: Nano pins drawn with pin_l/pin_r(x, y, "LABEL", physical), the
# variable name they are assigned to, and the module pins they are wired to.
sch_nano = {}
for var, label, num in re.findall(r'(n_\w+) = pin_[lr]\([^,]+, \d+, "([^"]+)", (\d+)\)', sch):
    sch_nano[var] = (label, int(num))
sch_mod = dict(re.findall(r'(m_\w+) = pin_l\([^,]+, \d+, "([^"]+)"', sch))
sch_wires = re.findall(r'wire\((n_\w+), (m_\w+)\)', sch)

# Wiring view: wire(net, [(px[("T"|"B", "PIN")] ...  and OLED pins by net name.
wir_pins = {}
# (a) loops over ("NET", "PIN") pairs; (b) wire("NET", [... px[("T", "PIN")] ...])
for net, p in re.findall(r'\("([A-Z+_0-9]+)", "([AD]\d+|5V|GND|VIN)"\)', wir):
    wir_pins.setdefault(net, set()).add(p)
for net, p in re.findall(r'wire\("([^"]+)", \[[^;]*?px\[\("[TB]", "([^"]+)"\)\]', wir, re.S):
    wir_pins.setdefault(net, set()).add(p)

for sig, macro, npin, mod, wnet in SIGNALS:
    num = int(npin[1:]) if npin.startswith("D") else None
    phys = NANO_PHYS.get(npin)
    # 1. firmware
    if macro:
        m = re.search(r"#define\s+%s\s+(\d+)" % macro, cfg)
        check(sig, "config.h", bool(m) and int(m.group(1)) == num,
              f"{macro} = {m.group(1) if m else 'missing'} (expected {num})")
    # 2. schematic: a Nano pin whose label starts with the pin name and whose
    #    physical number matches; and, for module signals, a wire to that label.
    hits = [(v, l, n) for v, (l, n) in sch_nano.items()
            if l.split(" / ")[0].replace("+", "") in (npin, npin.replace("D", "D"))
            or l.startswith(npin + " ")]
    if npin == "5V":
        hits = [(v, l, n) for v, (l, n) in sch_nano.items() if l == "+5V"]
    if sig != "STATUS_LED":
        ok = any(n == phys for _, _, n in hits)
        check(sig, "schematic", ok, f"{[(l, n) for _, l, n in hits]} (expected {npin} = pin {phys})")
        if mod and sig in ("SDA", "SCL"):
            # through the level shifter U4: Nano pin -> U4 HVn, U4 LVn -> module pin
            y = {"SDA": 460, "SCL": 500}[sig]
            nv = [v for v, _, _ in hits][0] if hits else "?"
            ok = (f"wire({nv}, (ux4, {y}))" in sch and
                  f"wire((ux4 + uw4, {y}), m_{sig.lower()})" in sch and
                  sch_mod.get(f"m_{sig.lower()}", "").startswith(mod))
            check(sig, "schematic wire", ok, f"{npin} -> U4 -> {mod}")
        elif mod:
            nvars = {v for v, _, _ in hits}
            wired = [sch_mod.get(m, "?") for nv, m in sch_wires if nv in nvars]
            check(sig, "schematic wire", any(w.startswith(mod) for w in wired),
                  f"{npin} wired to {wired} (expected {mod})")
    # 3. wiring view
    if wnet:
        label = {"5V": "5V"}.get(npin, npin)
        check(sig, "wiring.svg", label in wir_pins.get(wnet, set()),
              f"net {wnet} -> {sorted(wir_pins.get(wnet, set()))} (expected {label})")
    # 4. PINOUT.md section 3 table row: "| phys | **NAME** ..."
    if phys:
        pname = {"5V": r"\+5V", "VIN": "VIN"}.get(npin, npin)
        row = re.search(r"^\| %d \| \*\*%s\*\*[^\n]*" % (phys, pname), pin, re.M)
        if sig == "STATUS_LED":
            row = re.search(r"^\| %d \| %s [^\n]*" % (phys, npin), pin, re.M)
        ok = bool(row)
        if ok and macro:
            ok = f"`{macro} {num}`" in row.group(0)
        if ok and mod:
            ok = f"**{mod}**" in row.group(0)
        check(sig, "PINOUT.md", ok, row.group(0)[:70] if row else f"no row for pin {phys} {npin}")
    # 5. README build step 4 table (module wiring) and step 6 text
    if mod:
        if sig in ("SDA", "SCL"):  # via the level shifter U4
            r = re.search(r"^ *\| %s \| U4 LV\d [^|]*socket %s \(pin %d\)" % (mod, npin, phys), rd, re.M)
        else:
            r = re.search(r"^ *\| %s \| socket %s \(pin %d\)" % (mod, npin, phys), rd, re.M)
        check(sig, "README.md", bool(r), r.group(0) if r else f"no '| {mod} | socket {npin} (pin {phys})' row")
    elif sig in ("FAN_PWM", "TACH"):
        r = re.search(r"socket \*\*%s\*\* \(pin %d\)" % (npin, phys), rd)
        check(sig, "README.md", bool(r), r.group(0) if r else f"no 'socket **{npin}** (pin {phys})'")
    elif sig in ("VIN", "+5V"):
        word = {"VIN": r"\*\*VIN\*\* pin \(30\)", "+5V": r"\*\*\+5V\*\* pin \(27\)"}[sig]
        r = re.search(word, rd)
        check(sig, "README.md", bool(r), r.group(0) if r else f"no {word}")

# J1 pin functions: schematic, wiring view, PINOUT.md
j1 = {4: "+10V", 3: "GND", 2: "PWM", 1: "TACH"}
for n, f in j1.items():
    check(f"J1.{n}", "schematic", re.search(r'pin_r\([^)]*"%s", %d,' % (re.escape(f), n), sch) is not None, f)
    check(f"J1.{n}", "wiring.svg", re.search(r'%d: \("%s", \d+\)' % (n, re.escape(f)), wir) is not None, f)
    check(f"J1.{n}", "PINOUT.md", re.search(r"^\| \*\*%d\*\* \|" % n, pin, re.M) is not None, f)

w = max(len(r[0]) for r in rows)
for name, src, status, detail in rows:
    print(f"{name:<{w}}  {src:<15} {status:<8} {detail}")
print(f"\npin cross-check: {len(rows)} checks, {failures} mismatches")
sys.exit(1 if failures else 0)
